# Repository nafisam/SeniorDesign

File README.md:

# SeniorDesign
Senior Design project for UCF Spring 2021

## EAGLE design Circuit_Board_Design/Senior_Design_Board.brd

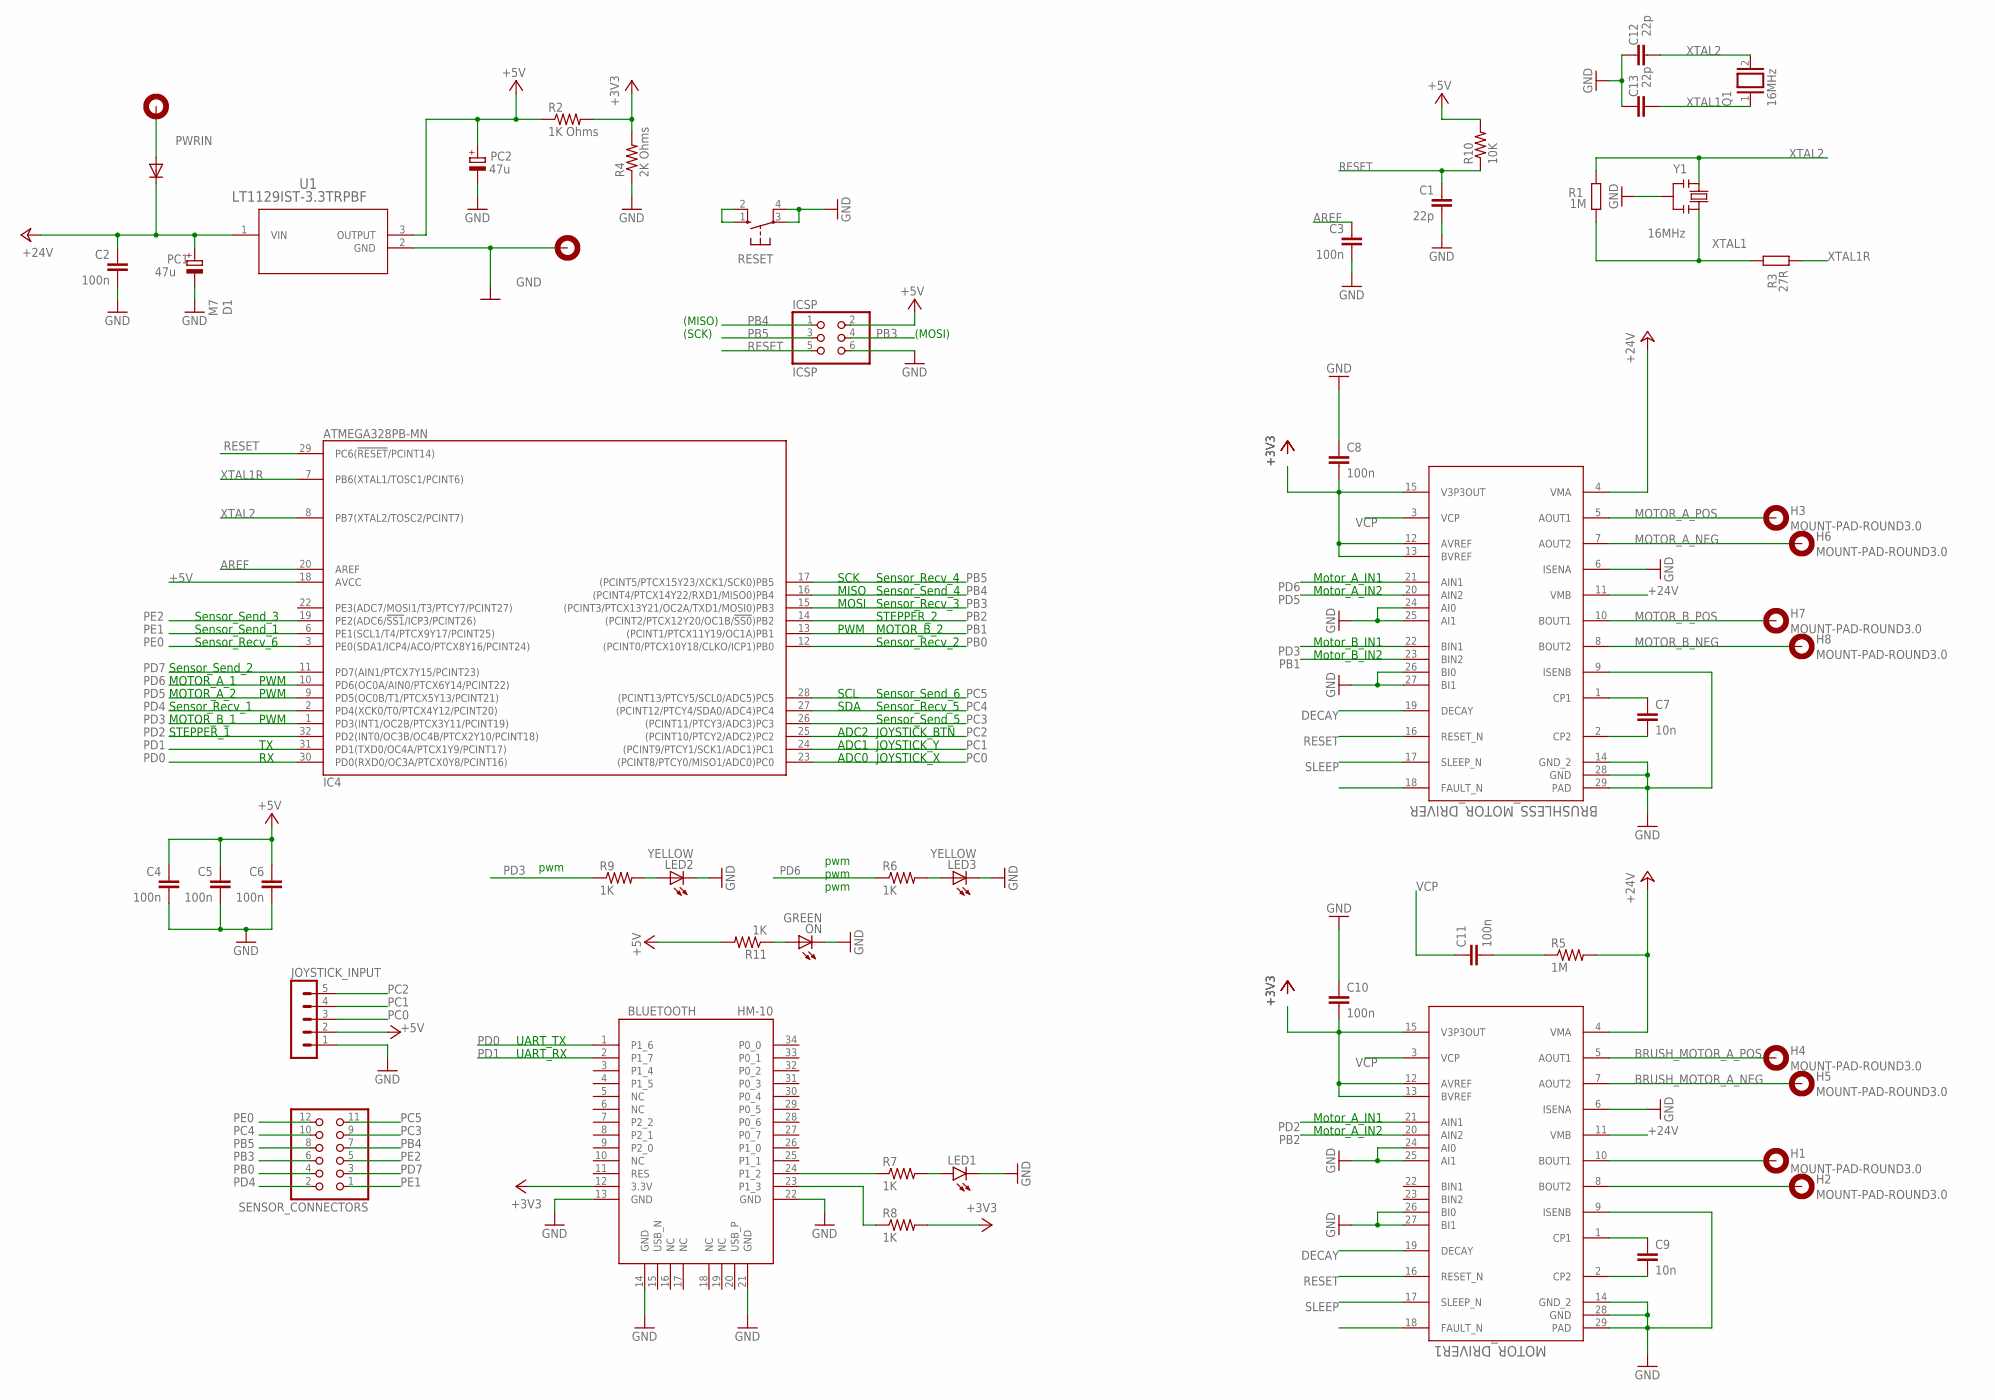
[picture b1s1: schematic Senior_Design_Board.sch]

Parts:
BATTERY_NEG: MOUNT-PAD-ROUND3.0; 3,0-PAD
BATTERY_POS: MOUNT-PAD-ROUND3.0; 3,0-PAD
BLUETOOTH: HM-10
BRUSHLESS_MOTOR_DRIVER: Value; PWP0028C_N
C1, C12, C13: 22p; C0603-ROUND
C2, C3, C4, C5, C6: 100n; C0603-ROUND
C7, C9: 10n; C2.5-3
C8, C10, C11: 100n; C2.5-3
D1: M7; SMB
H1, H2, H3, H4, H5, H6, H7, H8: MOUNT-PAD-ROUND3.0; 3,0-PAD
IC4: ATMEGA328PB-MN; QFN32_5X5_0.50
ICSP: ICSP; 2X03
JOYSTICK_INPUT: MA05-1
LED1: LEDCHIP-LED0805; CHIP-LED0805
LED2, LED3: YELLOW; CHIP-LED0805
MOTOR_DRIVER1: Value; PWP0028C_N
ON: GREEN; CHIP-LED0805
PC1, PC2: 47u; PANASONIC_D
Q1: 16MHz; QS
R1: 1M; R0603-ROUND
R2: 1K Ohms; 0204/7
R3: 27R; R0603-ROUND
R4: 2K Ohms; 0204/7
R5: 1M; 0204/7
R6, R9, R11: 1K; M0805
R7, R8: 1K; 0204/7
R10: 10K; M0805
RESET: 10-XX; B3F-10XX
SENSOR_CONNECTORS: PINHD-2X6; 2X06
U1: LT1129IST-3.3TRPBF; SOT-223_ST_LIT
Y1: 16MHz; RESONATOR

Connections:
+3V3: BLUETOOTH.12 (3.3V), R2.2, R4.2, R8.2
+5V: C4.1, C5.1, C6.1, IC4.18 (AVCC), ICSP.2, JOYSTICK_INPUT.2, PC2.+, R2.1, R10.2, R11.2, U1.3 (OUTPUT)
+24V: BRUSHLESS_MOTOR_DRIVER.4 (VMA), BRUSHLESS_MOTOR_DRIVER.11 (VMB), C2.1, D1.C, MOTOR_DRIVER1.4 (VMA), MOTOR_DRIVER1.11 (VMB), PC1.+, R5.2, U1.1 (VIN)
AREF: C3.1, IC4.20 (AREF)
BRUSH_MOTOR_A_NEG: H5.B3,0, MOTOR_DRIVER1.7 (AOUT2)
BRUSH_MOTOR_A_POS: H4.B3,0, MOTOR_DRIVER1.5 (AOUT1)
DECAY: BRUSHLESS_MOTOR_DRIVER.19 (DECAY), MOTOR_DRIVER1.19 (DECAY)
DRIVER_FAULT: BRUSHLESS_MOTOR_DRIVER.18 (FAULT_N)
DRIVER_FAULT1: MOTOR_DRIVER1.18 (FAULT_N)
GND: BATTERY_POS.B3,0, BLUETOOTH.13 (GND), BLUETOOTH.14 (GND), BLUETOOTH.21 (GND), BLUETOOTH.22 (GND), BRUSHLESS_MOTOR_DRIVER.6 (ISENA), BRUSHLESS_MOTOR_DRIVER.9 (ISENB), BRUSHLESS_MOTOR_DRIVER.14 (GND_2), BRUSHLESS_MOTOR_DRIVER.24 (AI0), BRUSHLESS_MOTOR_DRIVER.25 (AI1), BRUSHLESS_MOTOR_DRIVER.26 (BI0), BRUSHLESS_MOTOR_DRIVER.27 (BI1), BRUSHLESS_MOTOR_DRIVER.28 (GND), BRUSHLESS_MOTOR_DRIVER.29 (PAD), C1.2, C2.2, C3.2, C4.2, C5.2, C6.2, C8.1, C10.1, C12.2, C13.2, IC4.5 (GND), IC4.21 (GND), IC4.EXP (GND), ICSP.6, JOYSTICK_INPUT.1, LED1.C, LED2.C, LED3.C, MOTOR_DRIVER1.6 (ISENA), MOTOR_DRIVER1.9 (ISENB), MOTOR_DRIVER1.14 (GND_2), MOTOR_DRIVER1.24 (AI0), MOTOR_DRIVER1.25 (AI1), MOTOR_DRIVER1.26 (BI0), MOTOR_DRIVER1.27 (BI1), MOTOR_DRIVER1.28 (GND), MOTOR_DRIVER1.29 (PAD), ON.C, PC1.-, PC2.-, R4.1, RESET.3, RESET.4 (P1), U1.2 (GND), Y1.2
MOTOR_A_NEG: BRUSHLESS_MOTOR_DRIVER.7 (AOUT2), H6.B3,0
MOTOR_A_NEG1: H2.B3,0, MOTOR_DRIVER1.8 (BOUT2)
MOTOR_A_POS: BRUSHLESS_MOTOR_DRIVER.5 (AOUT1), H3.B3,0
MOTOR_B_NEG: BRUSHLESS_MOTOR_DRIVER.8 (BOUT2), H8.B3,0
MOTOR_B_POS: BRUSHLESS_MOTOR_DRIVER.10 (BOUT1), H7.B3,0
unnamed: LED2.A, R9.2
unnamed: ON.A, R11.1
unnamed: LED1.A, R7.2
unnamed: C9.1, MOTOR_DRIVER1.1 (CP1)
unnamed: BLUETOOTH.23 (P1_3), R8.1
unnamed: C9.2, MOTOR_DRIVER1.2 (CP2)
unnamed: C10.2, MOTOR_DRIVER1.12 (AVREF), MOTOR_DRIVER1.13 (BVREF), MOTOR_DRIVER1.15 (V3P3OUT)
unnamed: C11.2, R5.1
unnamed: H1.B3,0, MOTOR_DRIVER1.10 (BOUT1)
unnamed: BRUSHLESS_MOTOR_DRIVER.1 (CP1), C7.1
unnamed: BRUSHLESS_MOTOR_DRIVER.2 (CP2), C7.2
unnamed: BRUSHLESS_MOTOR_DRIVER.12 (AVREF), BRUSHLESS_MOTOR_DRIVER.13 (BVREF), BRUSHLESS_MOTOR_DRIVER.15 (V3P3OUT), C8.2
unnamed: BLUETOOTH.24 (P1_2), R7.1
PB0: IC4.12 ((PCINT0/PTCX10Y18/CLKO/ICP1)PB0), SENSOR_CONNECTORS.4
PB1: BRUSHLESS_MOTOR_DRIVER.23 (BIN2), IC4.13 ((PCINT1/PTCX11Y19/OC1A)PB1)
PB2: IC4.14 ((PCINT2/PTCX12Y20/OC1B/!SS0!)PB2), MOTOR_DRIVER1.20 (AIN2)
PB3: IC4.15 ((PCINT3/PTCX13Y21/OC2A/TXD1/MOSI0)PB3), ICSP.4, SENSOR_CONNECTORS.6
PB4: IC4.16 ((PCINT4/PTCX14Y22/RXD1/MISO0)PB4), ICSP.1, SENSOR_CONNECTORS.7
PB5: IC4.17 ((PCINT5/PTCX15Y23/XCK1/SCK0)PB5), ICSP.3, SENSOR_CONNECTORS.8
PC0: IC4.23 ((PCINT8/PTCY0/MISO1/ADC0)PC0), JOYSTICK_INPUT.3
PC1: IC4.24 ((PCINT9/PTCY1/SCK1/ADC1)PC1), JOYSTICK_INPUT.4
PC2: IC4.25 ((PCINT10/PTCY2/ADC2)PC2), JOYSTICK_INPUT.5
PC3: IC4.26 ((PCINT11/PTCY3/ADC3)PC3), SENSOR_CONNECTORS.9
PC4: IC4.27 ((PCINT12/PTCY4/SDA0/ADC4)PC4), SENSOR_CONNECTORS.10
PC5: IC4.28 ((PCINT13/PTCY5/SCL0/ADC5)PC5), SENSOR_CONNECTORS.11
PD0: BLUETOOTH.1 (P1_6), IC4.30 (PD0(RXD0/OC3A/PTCX0Y8/PCINT16))
PD1: BLUETOOTH.2 (P1_7), IC4.31 (PD1(TXD0/OC4A/PTCX1Y9/PCINT17))
PD2: IC4.32 (PD2(INT0/OC3B/OC4B/PTCX2Y10/PCINT18)), MOTOR_DRIVER1.21 (AIN1)
PD3: BRUSHLESS_MOTOR_DRIVER.22 (BIN1), IC4.1 (PD3(INT1/OC2B/PTCX3Y11/PCINT19)), R9.1
PD4: IC4.2 (PD4(XCK0/T0/PTCX4Y12/PCINT20)), SENSOR_CONNECTORS.2
PD5: BRUSHLESS_MOTOR_DRIVER.20 (AIN2), IC4.9 (PD5(OC0B/T1/PTCX5Y13/PCINT21))
PD6: BRUSHLESS_MOTOR_DRIVER.21 (AIN1), IC4.10 (PD6(OC0A/AIN0/PTCX6Y14/PCINT22)), R6.1
PD7: IC4.11 (PD7(AIN1/PTCX7Y15/PCINT23)), SENSOR_CONNECTORS.3
PE0: IC4.3 (PE0(SDA1/ICP4/ACO/PTCX8Y16/PCINT24)), SENSOR_CONNECTORS.12
PE1: IC4.6 (PE1(SCL1/T4/PTCX9Y17/PCINT25)), SENSOR_CONNECTORS.1
PE2: IC4.19 (PE2(ADC6/!SS1!/ICP3/PCINT26)), SENSOR_CONNECTORS.5
PWRIN: BATTERY_NEG.B3,0, D1.A
RESET: BRUSHLESS_MOTOR_DRIVER.16 (RESET_N), C1.1, IC4.29 (PC6(!RESET!/PCINT14)), ICSP.5, MOTOR_DRIVER1.16 (RESET_N), R10.1, RESET.1 (S), RESET.2 (S1)
SLEEP: BRUSHLESS_MOTOR_DRIVER.17 (SLEEP_N), MOTOR_DRIVER1.17 (SLEEP_N)
VCC: IC4.4 (VCC)
VCP: BRUSHLESS_MOTOR_DRIVER.3 (VCP), C11.1, MOTOR_DRIVER1.3 (VCP)
XTAL1: C13.1, Q1.1, R1.1, R3.2, Y1.3
XTAL1R: IC4.7 (PB6(XTAL1/TOSC1/PCINT6)), R3.1
XTAL2: C12.1, IC4.8 (PB7(XTAL2/TOSC2/PCINT7)), Q1.2, R1.2, Y1.1
Y_LED_POS: LED3.A, R6.2

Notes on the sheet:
(SCK)
(MISO)
(MOSI)
pwm
Motor_A_IN1
Motor_A_IN2
Motor_B_IN1
Motor_B_IN2
UART_RX
UART_TX
SCK
MISO
MOSI
SCL
SDA
PWM
ADC0
ADC1
ADC2
JOYSTICK_X
JOYSTICK_Y
JOYSTICK_BTN
MOTOR_A_1
MOTOR_A_2
MOTOR_B_1
MOTOR_B_2
Sensor_Send_1
Sensor_Recv_1
Sensor_Send_2
Sensor_Recv_2
Sensor_Send_3
Sensor_Recv_3
Sensor_Send_4
Sensor_Recv_4
Sensor_Send_5
Sensor_Recv_5
Sensor_Send_6
Sensor_Recv_6
STEPPER_1
STEPPER_2

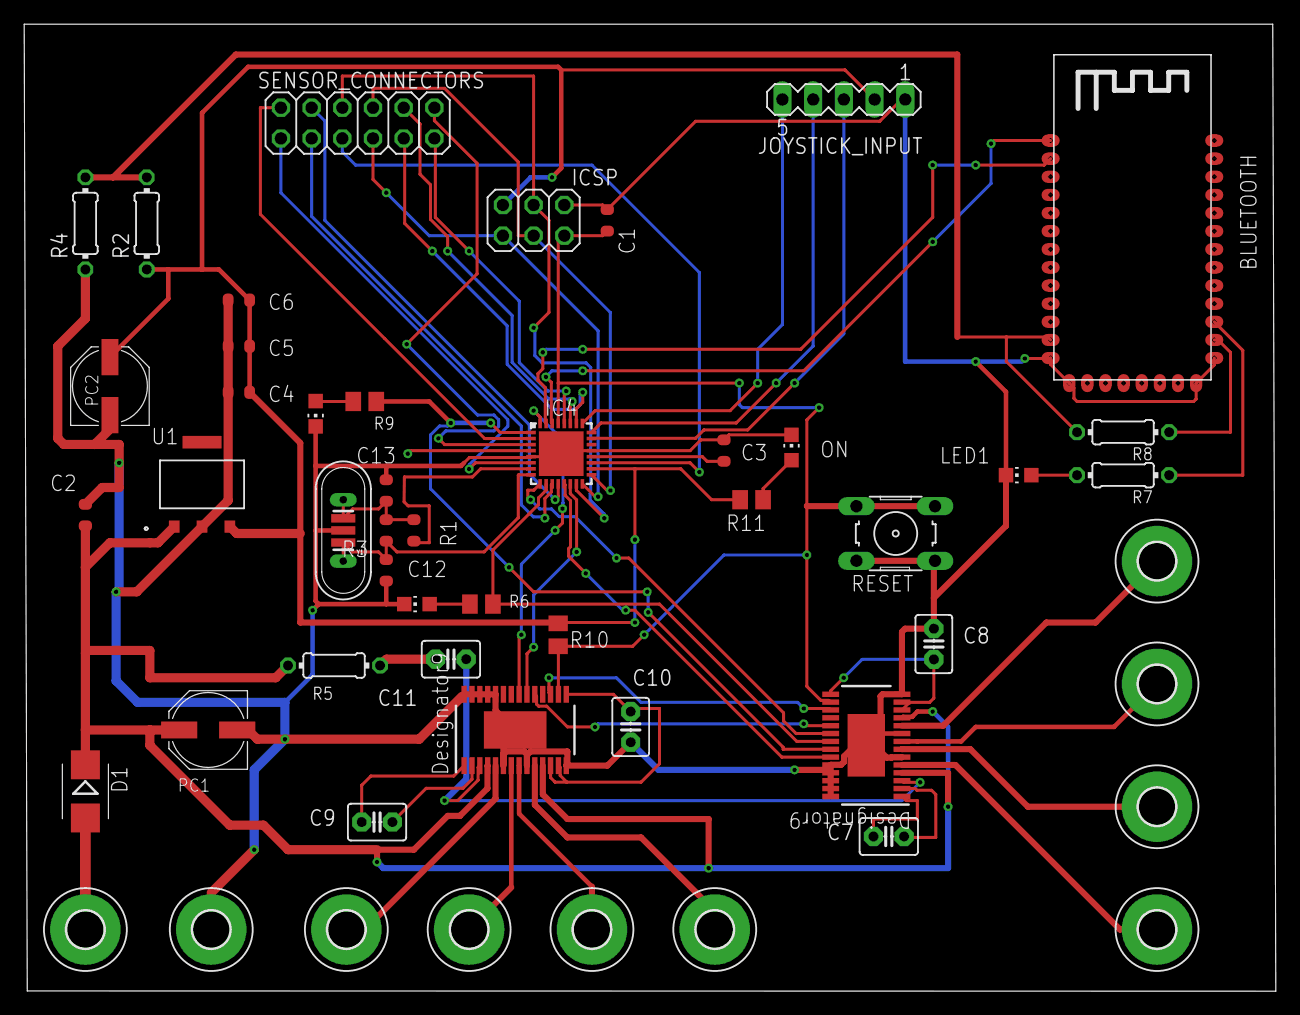
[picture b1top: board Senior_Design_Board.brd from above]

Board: 2 copper layers, 103.6 x 80.0 mm, 52 parts (0 on the bottom side), 57 nets.

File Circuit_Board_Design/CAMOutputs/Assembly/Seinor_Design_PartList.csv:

"Qty";"Value";"Device";"Package";"Parts";"Description";"ALTERNATE_PARTNUMBER";"APPLICATION_BUILDNUMBER";"BUILT_BY";"COMPTYPE";"MANUFACTURER";"MANUFACTURER_PART_NUMBER";"MF";"MOUNTTYPE";"MPN";"OC_FARNELL";"OC_NEWARK";"PACKAGEREFERENCE";"PARTNUMBER";"PIN_COUNT";"POPULARITY";"REFDES";"ROHS";"SOURCELIBRARY";"SPICEPREFIX";"TYPE";"VALUE";"VENDOR";
"1";"";"10-XX";"B3F-10XX";"RESET";"OMRON SWITCH";"";"";"";"";"";"";"";"";"B3F-1000";"176432";"36M3542";"";"";"";"72";"";"";"";"";"";"";"";
"1";"";"LEDCHIP-LED0805";"CHIP-LED0805";"LED1";"LED";"";"";"";"";"";"";"";"";"";"";"";"";"";"";"68";"";"";"";"";"";"";"";
"1";"";"MA05-1";"MA05-1";"JOYSTICK_INPUT";"PIN HEADER";"";"";"";"";"";"";"";"";"";"unknown";"unknown";"";"";"";"29";"";"";"";"";"";"";"";
"1";"";"PINHD-2X6";"2X06";"SENSOR_CONNECTORS";"PIN HEADER";"";"";"";"";"";"";"";"";"";"";"";"";"";"";"8";"";"";"";"";"";"";"";
"5";"100n";"C-EU0603-RND";"C0603-ROUND";"C2, C3, C4, C5, C6";"CAPACITOR, European symbol";"";"";"";"";"";"";"";"";"";"";"";"";"";"";"";"";"";"";"";"";"";"";
"3";"100n";"C2,5-3";"C2.5-3";"C8, C10, C11";"CAPACITOR";"";"";"";"";"";"";"";"";"";"";"";"";"";"";"38";"";"";"";"";"";"";"";
"1";"10K";"R-US_M0805";"M0805";"R10";"RESISTOR, American symbol";"";"";"";"";"";"";"";"";"";"";"";"";"";"";"45";"";"";"";"R";"";"";"";
"2";"10n";"C2,5-3";"C2.5-3";"C7, C9";"CAPACITOR";"";"";"";"";"";"";"";"";"";"";"";"";"";"";"38";"";"";"";"";"";"";"";
"1";"16MHz";"RESONATORMU";"RESONATOR";"Y1";"";"";"";"";"";"";"";"";"";"";"";"";"";"";"";"";"";"";"";"";"";"";"";
"1";"16MHz";"XTAL/S";"QS";"Q1";"CRYSTAL";"";"";"";"";"";"";"";"";"";"";"";"";"";"";"";"";"";"";"";"";"";"";
"2";"1K";"R-US_0204/7";"0204/7";"R7, R8";"RESISTOR, American symbol";"";"";"";"";"";"";"";"";"";"";"";"";"";"";"48";"";"";"";"R";"";"";"";
"3";"1K";"R-US_M0805";"M0805";"R6, R9, R11";"RESISTOR, American symbol";"";"";"";"";"";"";"";"";"";"";"";"";"";"";"45";"";"";"";"R";"";"";"";
"1";"1K Ohms";"R-US_0204/7";"0204/7";"R2";"RESISTOR, American symbol";"";"";"";"";"";"";"";"";"";"";"";"";"";"";"48";"";"";"";"R";"";"";"";
"1";"1M";"R-EU_R0603";"R0603-ROUND";"R1";"RESISTOR, European symbol";"";"";"";"";"";"";"";"";"";"";"";"";"";"";"";"";"";"";"";"";"";"";
"1";"1M";"R-US_0204/7";"0204/7";"R5";"RESISTOR, American symbol";"";"";"";"";"";"";"";"";"";"";"";"";"";"";"48";"";"";"";"R";"";"";"";
"3";"22p";"C-EU0603-RND";"C0603-ROUND";"C1, C12, C13";"CAPACITOR, European symbol";"";"";"";"";"";"";"";"";"";"";"";"";"";"";"";"";"";"";"";"";"";"";
"1";"27R";"R-EU_R0603";"R0603-ROUND";"R3";"RESISTOR, European symbol";"";"";"";"";"";"";"";"";"";"";"";"";"";"";"";"";"";"";"";"";"";"";
"1";"2K Ohms";"R-US_0204/7";"0204/7";"R4";"RESISTOR, American symbol";"";"";"";"";"";"";"";"";"";"";"";"";"";"";"48";"";"";"";"R";"";"";"";
"2";"47u";"CPOL-EUD";"PANASONIC_D";"PC1, PC2";"POLARIZED CAPACITOR, European symbol";"";"";"";"";"";"";"";"";"";"";"";"";"";"";"";"";"";"";"";"";"";"";
"1";"ATMEGA328PB-MN";"ATMEGA328PB-MN";"QFN32_5X5_0.50";"IC4";"8-bit AVR Microcontroller";"";"";"";"";"";"";"";"";"";"";"";"";"";"";"";"";"";"";"";"";"";"";
"1";"GREEN";"LEDCHIP-LED0805";"CHIP-LED0805";"ON";"LED";"";"";"";"";"";"";"";"";"";"";"";"";"";"";"";"";"";"";"";"";"";"";
"1";"HM-10";"HM-10";"HM-10";"BLUETOOTH";"";"";"";"";"";"";"";"";"";"";"";"";"";"";"";"";"";"";"";"";"";"";"";
"1";"ICSP";"PINHD-2X3";"2X03";"ICSP";"PIN HEADER";"";"";"";"";"";"";"";"";"";"";"";"";"";"";"";"";"";"";"";"";"";"";
"1";"LT1129IST-3.3TRPBF";"LT1129IST-3.3TRPBF";"SOT-223_ST_LIT";"U1";"";"";"";"EMA_UL_Team";"";"";"LT1129IST-3.3#TRPBF";"";"";"";"";"";"";"";"";"";"";"";"LinearTech_2016-05-13_2";"";"";"";"Linear Technology";
"1";"M7";"DIODE-SMB";"SMB";"D1";"DIODE";"";"";"";"";"";"";"";"";"";"";"";"";"";"";"";"";"";"";"";"";"";"";
"10";"MOUNT-PAD-ROUND3.0";"MOUNT-PAD-ROUND3.0";"3,0-PAD";"BATTERY_NEG, BATTERY_POS, H1, H2, H3, H4, H5, H6, H7, H8";"MOUNTING PAD, round";"";"";"";"";"";"";"";"";"";"";"";"";"";"";"17";"";"";"";"";"";"";"";
"2";"Value";"DRV8841PWP";"PWP0028C_N";"BRUSHLESS_MOTOR_DRIVER, MOTOR_DRIVER1";"";"DRV8841PWP";"*";"";"IC";"Texas Instruments";"";"";"SMT";"";"";"";"PWP0028C";"DRV8841PWPR";"29";"";"RefDes";"Y";"";"";"TYPE";"Value";"";
"2";"YELLOW";"LEDCHIP-LED0805";"CHIP-LED0805";"LED2, LED3";"LED";"";"";"";"";"";"";"";"";"";"";"";"";"";"";"";"";"";"";"";"";"";"";

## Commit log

2021-03-05 Adding initial files
2021-04-06 Green Team Senior Design Code
2021-04-06 Green Team Definitions
2021-04-06 Changes from April 5th
    - Moved Pin Definition around to match Green Team's board
    - Finalized Sensor Code
    - Updated Turning code to work with a new H-bridge instead of Zero Turn Radius
    - Changed Bluetooth baud rate to the M2 spec.
2021-04-11 Updates from April 11th
    Final working code for Green team's car
